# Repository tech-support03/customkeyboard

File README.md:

# customkeyboard

## A custom hotswapable keyboard with a 60% plus arrow keys layout

The purpose of this project was to learn about designing pcbs and how to make my own keyboard. I wanted to make something that was not a completely unique design but I wanted my own personal touch. It had to be small and portable, so I went with a 60% layout at first. However I really wanted arrow keys because they are very important to me in a keyboard layout, so I added them and it acutally led to better packaging overall. Another very important thing to me was hotswapability. I wanted the ability to change my switches if I wanted to. This led to its own set of challenges, but eventually it worked out pretty nicely. Additionally, I wanted a rotary encoder, so I put one in the top left corner. Finally, I wanted the microcontroller to be exposed because I think it looks pretty cool, so I made a cutout for it in the top right. Overall, this project was really fun to design!

### CAD
Full CAD

Top Plate

Base

PCB (Hotswap sockets!)

### PCB

Layout

Schematic

### BOM

| Item                          | Description                                           | Link                                                                                 | Price | Quantity | Total |
|-------------------------------|-------------------------------------------------------|--------------------------------------------------------------------------------------|-------|----------|-------|
| PCB                           | circuit board for all the components                  | https://jlcpcb.com                                                                    | 20.70 | 1        | 22.64 |
| Raspberry Pi Pico             | Microcontroller for keyboard                          | https://www.microcenter.com/product/661033/raspberry-pi-pico-microcontroller-development-board    | 2.99  | 1        | 3.27 |
| Akko Cream Blue Switches      | Tactile switches for keyboard, sold in packs of 45    | https://www.amazon.com/Akko-Cream-Blue-Tactile-Switches/dp/B0CL4FRWY8                 | 25.98 | 1        | 28.41 |
| Womier Black keycaps          | Keycaps for keyboard                                  | https://www.amazon.com/Womier-Black-Pudding-Keycaps/dp/B0BN5F3B9S                     | 17.99 | 1        | 19.67 |
| Plate mount Stabilizers       | Stabilizers for keyboard                              | https://www.amazon.com/Durock-Plate-Mount-Stabilizer/dp/B08T6CTRM8                    | 9.99  | 1        | 10.92  |
| Kailh hotswap sockets         | Sockets for hot-swappable switches                    | https://www.amazon.com/Kailh-Hot-Swap-Sockets/dp/B07ZHYJWLJ                           | 9.99  | 1        | 10.92 |
| 1N4148 Diodes                 | Diodes for the keyboard matrix                        | https://www.amazon.com/ALLECIN-1N4148-Schottky-Diodes/dp/B0BRF4SJGQ                   | 5.99  | 1        | 6.55 |
| EC11 Rotary Encoder with switch | Rotary encoder used for volume knob                 | https://keeb.io/products/rotary-encoder-ec11                                          | 1.99  | 1        | 2.18  |
| **Total:**                    |                                                       |                                                                                      |       |          | **104.56** |

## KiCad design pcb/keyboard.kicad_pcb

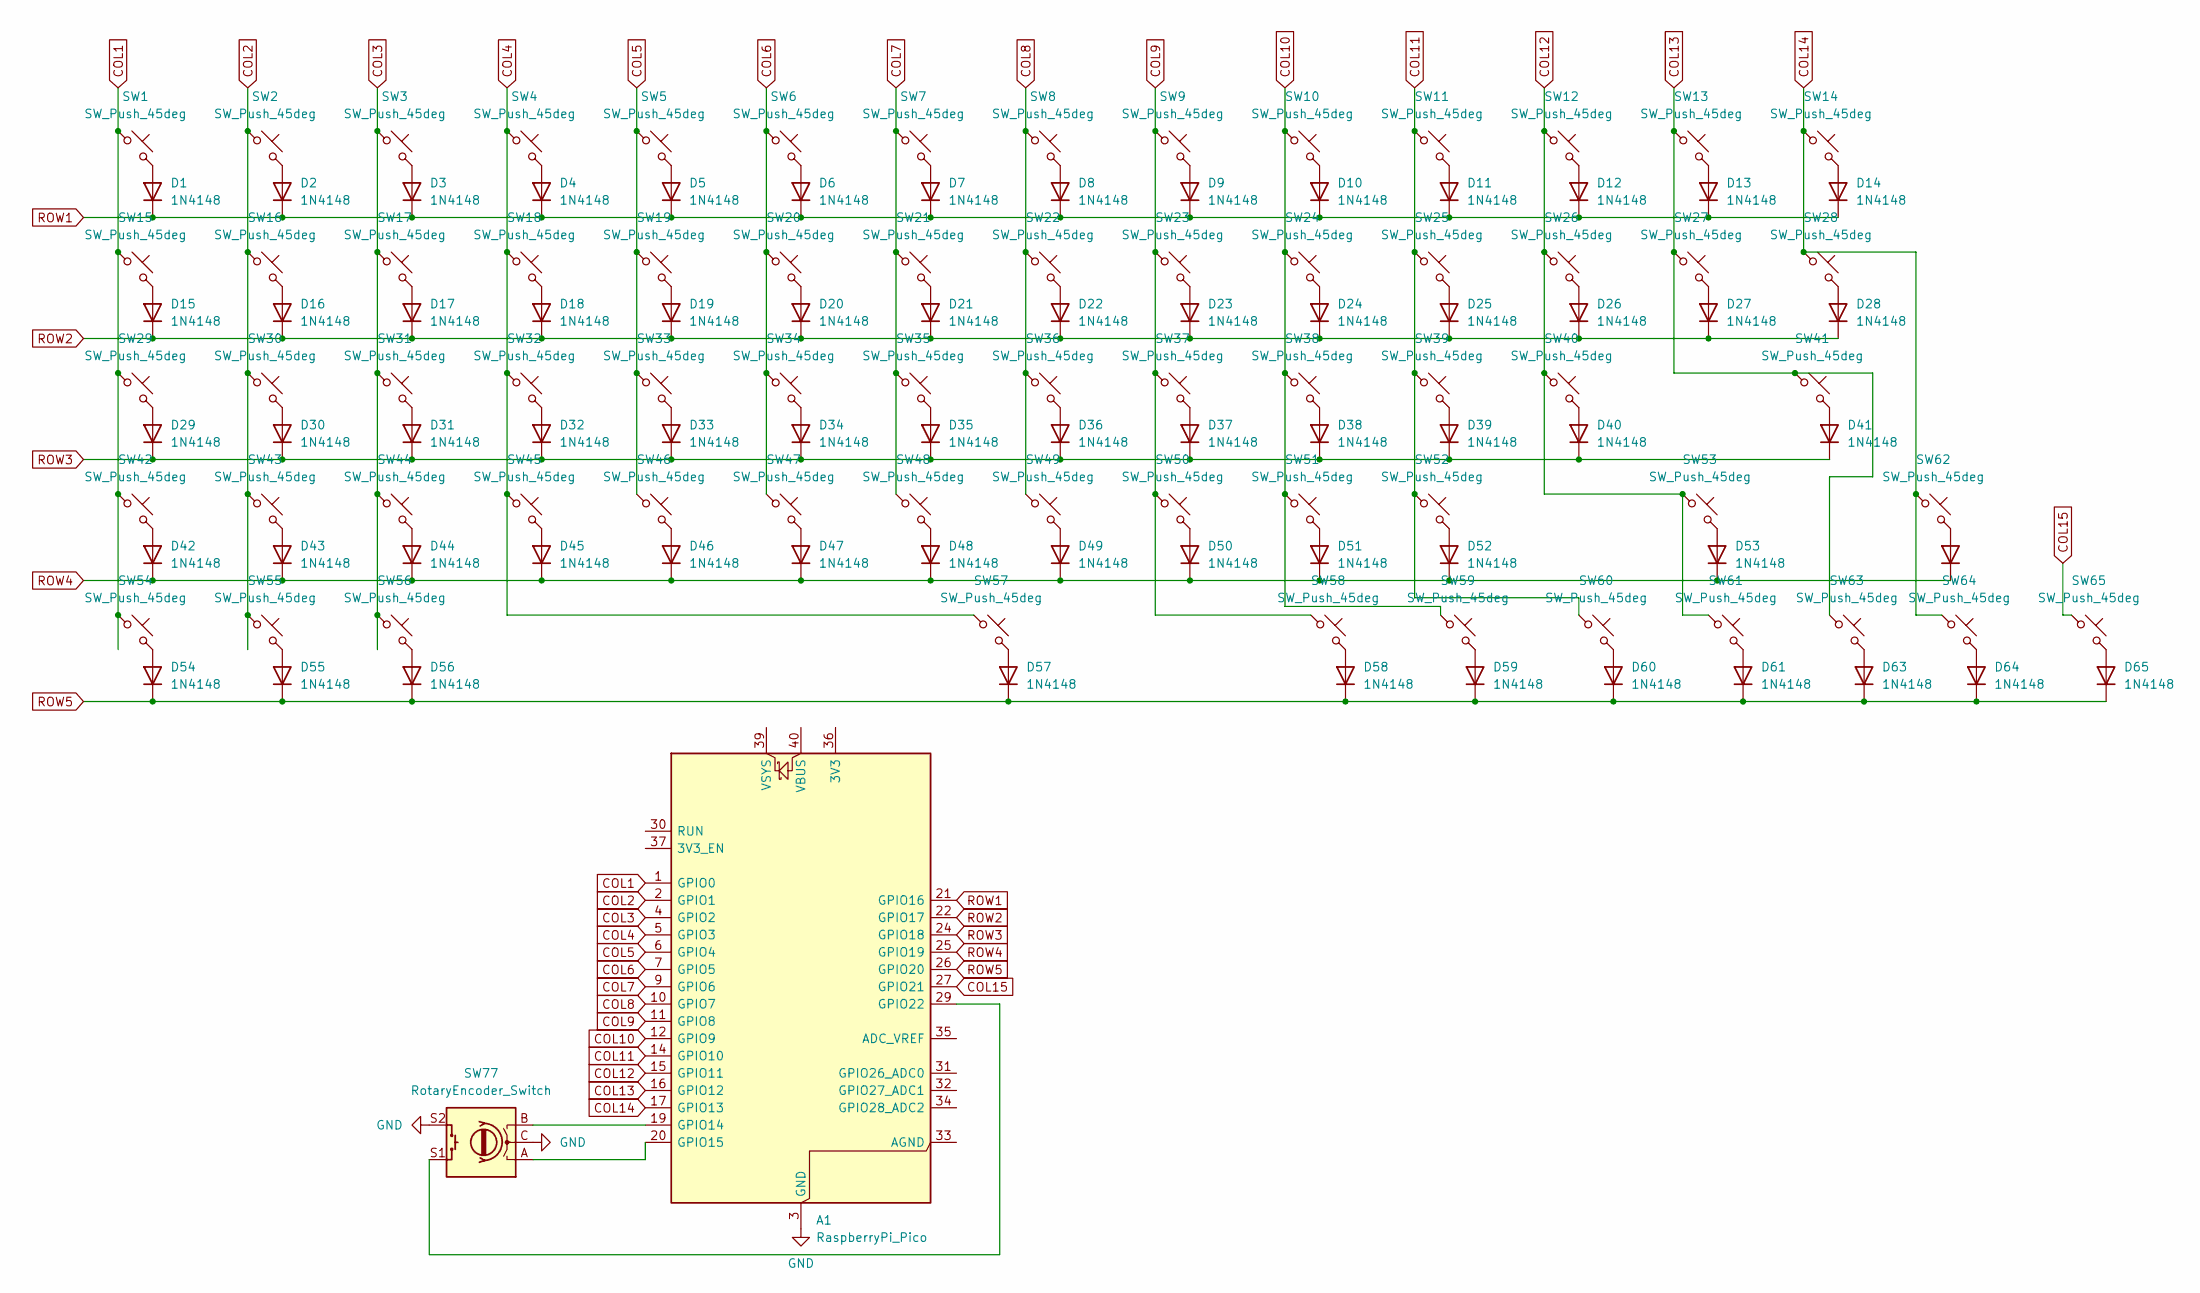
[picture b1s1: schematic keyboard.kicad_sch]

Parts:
A1: RaspberryPi_Pico; RaspberryPi_Pico_Common_Unspecified
D1, D2, D3, D4, D5, D6, D7, D8, D9, D10, D11, D12, D13, D14, D15, D16, D17, D18, D19, D20, D21, D22, D23, D24, D25, D26, D27, D28, D29, D30, D31, D32, D33, D34, D35, D36, D37, D38, D39, D40, D41, D42, D43, D44, D45, D46, D47, D48, D49, D50, D51, D52, D53, D54, D55, D56, D57, D58, D59, D60, D61, D62, D63, D64, D65: 1N4148; D_DO-35_SOD27_P7.62mm_Horizontal
SW1, SW2, SW3, SW4, SW5, SW6, SW7, SW8, SW9, SW10, SW11, SW12, SW13, SW16, SW17, SW18, SW19, SW20, SW21, SW22, SW23, SW24, SW25, SW26, SW27, SW30, SW31, SW32, SW33, SW34, SW35, SW36, SW37, SW38, SW39, SW40, SW43, SW44, SW45, SW46, SW47, SW48, SW49, SW50, SW51, SW52, SW62, SW63, SW64, SW65: SW_Push_45deg; SW_Hotswap_Kailh_MX_1.00u
SW14: SW_Push_45deg; SW_Hotswap_Kailh_MX_2.00u
SW15, SW28: SW_Push_45deg; SW_Hotswap_Kailh_MX_1.50u
SW29: SW_Push_45deg; SW_Hotswap_Kailh_MX_1.75u
SW41, SW42: SW_Push_45deg; SW_Hotswap_Kailh_MX_2.25u
SW53: SW_Push_45deg; SW_Hotswap_Kailh_MX_2.75u
SW54, SW55, SW56, SW58, SW59, SW60, SW61: SW_Push_45deg; SW_Hotswap_Kailh_MX_1.25u
SW57: SW_Push_45deg; SW_Hotswap_Kailh_MX_6.25u
SW77: RotaryEncoder_Switch; RotaryEncoder_Alps_EC11E-Switch_Vertical_H20mm

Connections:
COL1: A1.1 (GPIO0), SW1.1, SW15.1, SW29.1, SW42.1, SW54.1
COL2: A1.2 (GPIO1), SW2.1, SW16.1, SW30.1, SW43.1, SW55.1
COL3: A1.4 (GPIO2), SW3.1, SW17.1, SW31.1, SW44.1, SW56.1
COL4: A1.5 (GPIO3), SW4.1, SW18.1, SW32.1, SW45.1, SW57.1
COL5: A1.6 (GPIO4), SW5.1, SW19.1, SW33.1, SW46.1
COL6: A1.7 (GPIO5), SW6.1, SW20.1, SW34.1, SW47.1
COL7: A1.9 (GPIO6), SW7.1, SW21.1, SW35.1, SW48.1
COL8: A1.10 (GPIO7), SW8.1, SW22.1, SW36.1, SW49.1
COL9: A1.11 (GPIO8), SW9.1, SW23.1, SW37.1, SW50.1, SW58.1
COL10: A1.12 (GPIO9), SW10.1, SW24.1, SW38.1, SW51.1, SW59.1
COL11: A1.14 (GPIO10), SW11.1, SW25.1, SW39.1, SW52.1, SW60.1
COL12: A1.15 (GPIO11), SW12.1, SW26.1, SW40.1, SW53.1, SW61.1
COL13: A1.16 (GPIO12), SW13.1, SW27.1, SW41.1, SW63.1
COL14: A1.17 (GPIO13), SW14.1, SW28.1, SW62.1, SW64.1
COL15: A1.27 (GPIO21), SW65.1
GND: A1.3 (GND), A1.8 (GND), A1.13 (GND), A1.18 (GND), A1.23 (GND), A1.28 (GND), A1.38 (GND), SW77.C, SW77.S2
unnamed: A1.19 (GPIO14), SW77.B
unnamed: A1.20 (GPIO15), SW77.A
unnamed: A1.29 (GPIO22), SW77.S1
unnamed: D1.2 (A), SW1.2
unnamed: D2.2 (A), SW2.2
unnamed: D3.2 (A), SW3.2
unnamed: D4.2 (A), SW4.2
unnamed: D5.2 (A), SW5.2
unnamed: D6.2 (A), SW6.2
unnamed: D7.2 (A), SW7.2
unnamed: D8.2 (A), SW8.2
unnamed: D9.2 (A), SW9.2
unnamed: D10.2 (A), SW10.2
unnamed: D11.2 (A), SW11.2
unnamed: D12.2 (A), SW12.2
unnamed: D13.2 (A), SW13.2
unnamed: D14.2 (A), SW14.2
unnamed: D15.2 (A), SW15.2
unnamed: D16.2 (A), SW16.2
unnamed: D17.2 (A), SW17.2
unnamed: D18.2 (A), SW18.2
unnamed: D19.2 (A), SW19.2
unnamed: D20.2 (A), SW20.2
unnamed: D21.2 (A), SW21.2
unnamed: D22.2 (A), SW22.2
unnamed: D23.2 (A), SW23.2
unnamed: D24.2 (A), SW24.2
unnamed: D25.2 (A), SW25.2
unnamed: D26.2 (A), SW26.2
unnamed: D27.2 (A), SW27.2
unnamed: D28.2 (A), SW28.2
unnamed: D29.2 (A), SW29.2
unnamed: D30.2 (A), SW30.2
unnamed: D31.2 (A), SW31.2
unnamed: D32.2 (A), SW32.2
unnamed: D33.2 (A), SW33.2
unnamed: D34.2 (A), SW34.2
unnamed: D35.2 (A), SW35.2
unnamed: D36.2 (A), SW36.2
unnamed: D37.2 (A), SW37.2
unnamed: D38.2 (A), SW38.2
unnamed: D39.2 (A), SW39.2
unnamed: D40.2 (A), SW40.2
unnamed: D41.2 (A), SW41.2
unnamed: D42.2 (A), SW42.2
unnamed: D43.2 (A), SW43.2
unnamed: D44.2 (A), SW44.2
unnamed: D45.2 (A), SW45.2
unnamed: D46.2 (A), SW46.2
unnamed: D47.2 (A), SW47.2
unnamed: D48.2 (A), SW48.2
unnamed: D49.2 (A), SW49.2
unnamed: D50.2 (A), SW50.2
unnamed: D51.2 (A), SW51.2
unnamed: D52.2 (A), SW52.2
unnamed: D53.2 (A), SW53.2
unnamed: D54.2 (A), SW54.2
unnamed: D55.2 (A), SW55.2
unnamed: D56.2 (A), SW56.2
unnamed: D57.2 (A), SW57.2
unnamed: D58.2 (A), SW58.2
unnamed: D59.2 (A), SW59.2
unnamed: D60.2 (A), SW60.2
unnamed: D61.2 (A), SW61.2
unnamed: D62.2 (A), SW62.2
unnamed: D63.2 (A), SW63.2
unnamed: D64.2 (A), SW64.2
unnamed: D65.2 (A), SW65.2
ROW1: A1.21 (GPIO16), D1.1 (K), D2.1 (K), D3.1 (K), D4.1 (K), D5.1 (K), D6.1 (K), D7.1 (K), D8.1 (K), D9.1 (K), D10.1 (K), D11.1 (K), D12.1 (K), D13.1 (K), D14.1 (K)
ROW2: A1.22 (GPIO17), D15.1 (K), D16.1 (K), D17.1 (K), D18.1 (K), D19.1 (K), D20.1 (K), D21.1 (K), D22.1 (K), D23.1 (K), D24.1 (K), D25.1 (K), D26.1 (K), D27.1 (K), D28.1 (K)
ROW3: A1.24 (GPIO18), D29.1 (K), D30.1 (K), D31.1 (K), D32.1 (K), D33.1 (K), D34.1 (K), D35.1 (K), D36.1 (K), D37.1 (K), D38.1 (K), D39.1 (K), D40.1 (K), D41.1 (K)
ROW4: A1.25 (GPIO19), D42.1 (K), D43.1 (K), D44.1 (K), D45.1 (K), D46.1 (K), D47.1 (K), D48.1 (K), D49.1 (K), D50.1 (K), D51.1 (K), D52.1 (K), D53.1 (K), D62.1 (K)
ROW5: A1.26 (GPIO20), D54.1 (K), D55.1 (K), D56.1 (K), D57.1 (K), D58.1 (K), D59.1 (K), D60.1 (K), D61.1 (K), D63.1 (K), D64.1 (K), D65.1 (K)

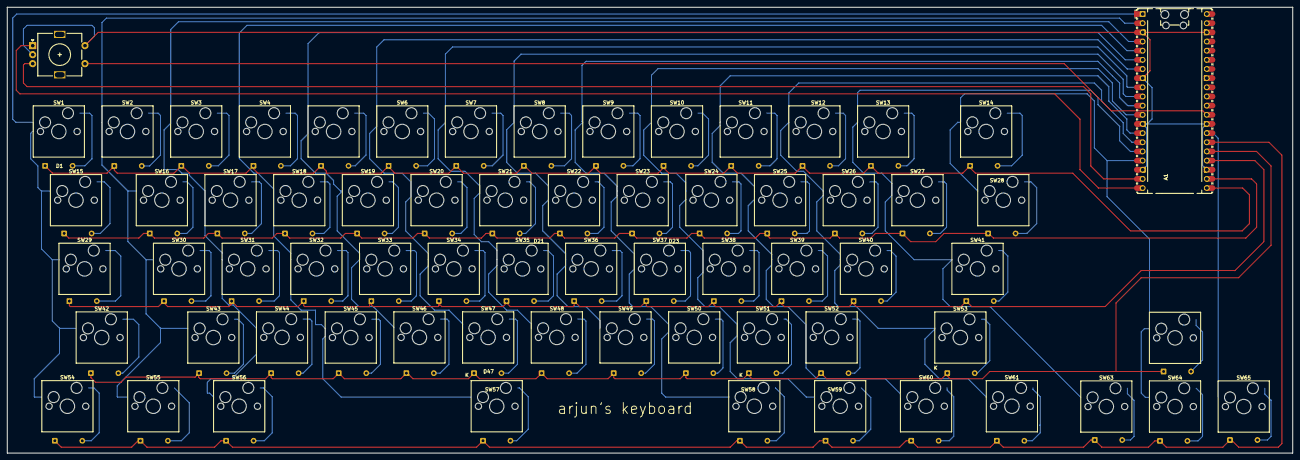
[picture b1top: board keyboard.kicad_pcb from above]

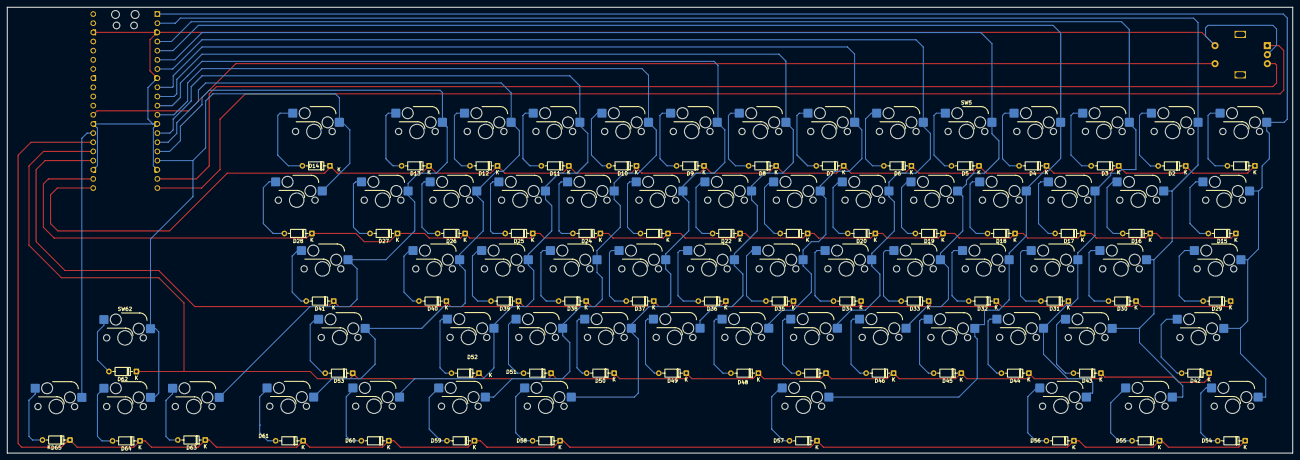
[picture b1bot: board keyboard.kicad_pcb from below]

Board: 2 copper layers, 356.5 x 123.6 mm, 132 parts (65 on the bottom side), 89 nets.

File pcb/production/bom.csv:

Designator,Footprint,Quantity,Value,LCSC Part #
A1,RaspberryPi_Pico_Common_Unspecified,1,RaspberryPi_Pico,
"D1, D10, D11, D12, D13, D14, D15, D16, D17, D18, D19, D2, D20, D21, D22, D23, D24, D25, D26, D27, D28, D29, D3, D30, D31, D32, D33, D34, D35, D36, D37, D38, D39, D4, D40, D41, D42, D43, D44, D45, D46, D47, D48, D49, D5, D50, D51, D52, D53, D54, D55, D56, D57, D58, D59, D6, D60, D61, D62, D63, D64, D65, D7, D8, D9",D_DO-35_SOD27_P7.62mm_Horizontal,65,1N4148,
"SW1, SW10, SW11, SW12, SW13, SW16, SW17, SW18, SW19, SW2, SW20, SW21, SW22, SW23, SW24, SW25, SW26, SW27, SW3, SW30, SW31, SW32, SW33, SW34, SW35, SW36, SW37, SW38, SW39, SW4, SW40, SW43, SW44, SW45, SW46, SW47, SW48, SW49, SW5, SW50, SW51, SW52, SW6, SW62, SW63, SW64, SW65, SW7, SW8, SW9",SW_Hotswap_Kailh_MX_1.00u,50,SW_Push_45deg,
SW14,SW_Hotswap_Kailh_MX_2.00u,1,SW_Push_45deg,
"SW15, SW28",SW_Hotswap_Kailh_MX_1.50u,2,SW_Push_45deg,
SW29,SW_Hotswap_Kailh_MX_1.75u,1,SW_Push_45deg,
"SW41, SW42",SW_Hotswap_Kailh_MX_2.25u,2,SW_Push_45deg,
SW53,SW_Hotswap_Kailh_MX_2.75u,1,SW_Push_45deg,
"SW54, SW55, SW56, SW58, SW59, SW60, SW61",SW_Hotswap_Kailh_MX_1.25u,7,SW_Push_45deg,
SW57,SW_Hotswap_Kailh_MX_6.25u,1,SW_Push_45deg,
SW77,RotaryEncoder_Alps_EC11E-Switch_Vertical_H20mm,1,RotaryEncoder_Switch,

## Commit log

2025-12-04 Add base and top plate files
2025-12-04 add full keyboard CAD
    the STEP file was too big for github so had to compress into a zip
2025-12-04 move file?
2025-12-04 Add all PCB files
2025-12-04 Add configuration for keyboard firmware
2025-12-04 Add info.json for keyboard configuration
2025-12-04 Add rules.mk for firmware configuration
2025-12-04 Add keymap and rotary encoder functionality
    Define keymaps for a 60% keyboard layout and implement rotary encoder handling.
2025-12-04 updated pcb files
2025-12-05 add journal
2025-12-05 Enhance README with project details and images
    Expanded project description and added CAD, PCB, and BOM sections with images and details.
2025-12-05 Add images to CAD section in README
    Added additional images to the CAD section of the README.
2025-12-05 Correct time entry for 12/4
    Updated time spent on 12/4 from 4 hours to 3 hours.
2025-12-05 Update README with enhanced project description
    Revised project description for clarity and detail.
2025-12-05 Revise BOM prices and total calculations
    Updated prices and totals for BOM items.
